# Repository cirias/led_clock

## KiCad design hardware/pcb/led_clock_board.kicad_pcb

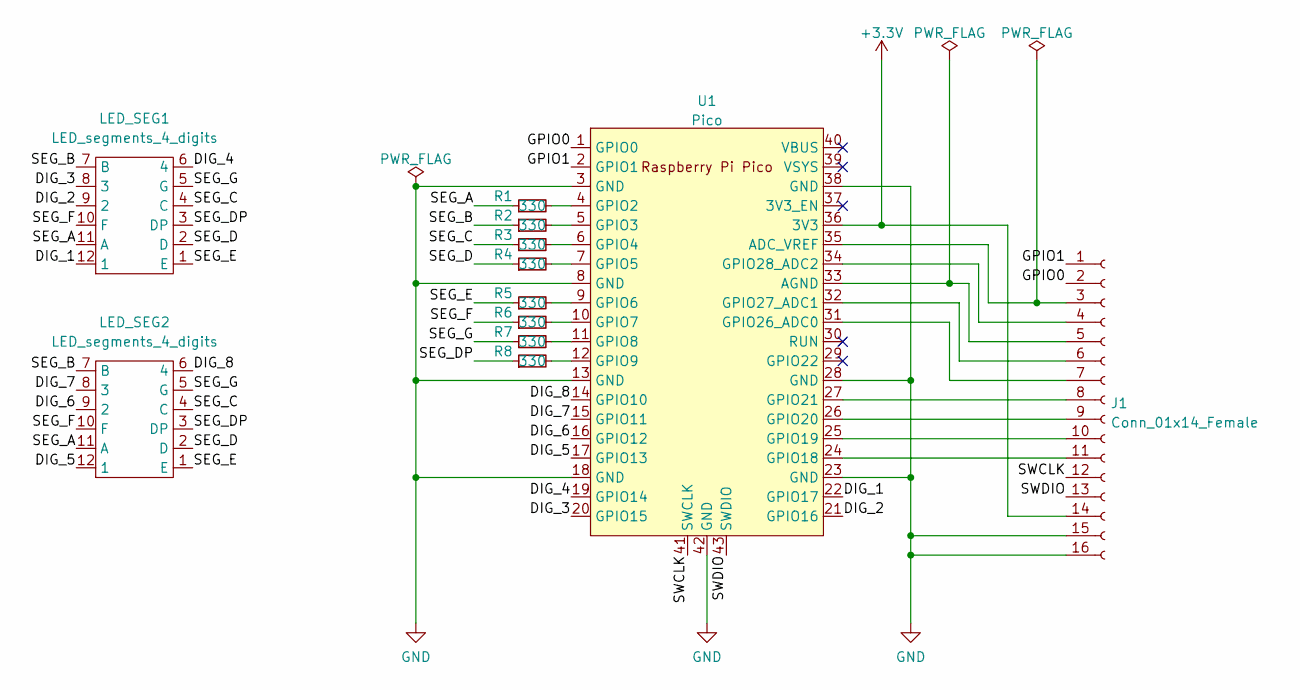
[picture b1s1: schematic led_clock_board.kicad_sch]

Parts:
J1: Conn_01x14_Female; PinHeader_1x16_P2.54mm_Vertical
LED_SEG1, LED_SEG2: LED_segments_4_digits
R1, R2, R3, R4, R5, R6, R7, R8: 330; R_Axial_DIN0207_L6.3mm_D2.5mm_P7.62mm_Horizontal
U1: Pico; RPi_Pico_SMD_TH

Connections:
+3V3: J1.14, U1.36 (3V3)
/DIG_1: LED_SEG1.12 (1), U1.22 (GPIO17)
/DIG_2: LED_SEG1.9 (2), U1.21 (GPIO16)
/DIG_3: LED_SEG1.8 (3), U1.20 (GPIO15)
/DIG_4: LED_SEG1.6 (4), U1.19 (GPIO14)
/DIG_5: LED_SEG2.12 (1), U1.17 (GPIO13)
/DIG_6: LED_SEG2.9 (2), U1.16 (GPIO12)
/DIG_7: LED_SEG2.8 (3), U1.15 (GPIO11)
/DIG_8: LED_SEG2.6 (4), U1.14 (GPIO10)
/GPIO0: J1.2, U1.1 (GPIO0)
/GPIO1: J1.1, U1.2 (GPIO1)
/SEG_A: LED_SEG1.11 (A), LED_SEG2.11 (A), R1.1
/SEG_B: LED_SEG1.7 (B), LED_SEG2.7 (B), R2.1
/SEG_C: LED_SEG1.4 (C), LED_SEG2.4 (C), R3.1
/SEG_D: LED_SEG1.2 (D), LED_SEG2.2 (D), R4.1
/SEG_DP: LED_SEG1.3 (DP), LED_SEG2.3 (DP), R8.1
/SEG_E: LED_SEG1.1 (E), LED_SEG2.1 (E), R5.1
/SEG_F: LED_SEG1.10 (F), LED_SEG2.10 (F), R6.1
/SEG_G: LED_SEG1.5 (G), LED_SEG2.5 (G), R7.1
/SWCLK: J1.12, U1.41 (SWCLK)
/SWDIO: J1.13, U1.43 (SWDIO)
GND: J1.15, J1.16, U1.3 (GND), U1.8 (GND), U1.13 (GND), U1.18 (GND), U1.23 (GND), U1.28 (GND), U1.38 (GND), U1.42 (GND)
unnamed: J1.3, U1.35 (ADC_VREF)
unnamed: J1.4, U1.34 (GPIO28_ADC2)
unnamed: J1.5, U1.33 (AGND)
unnamed: J1.6, U1.32 (GPIO27_ADC1)
unnamed: J1.7, U1.31 (GPIO26_ADC0)
unnamed: J1.8, U1.27 (GPIO21)
unnamed: J1.9, U1.26 (GPIO20)
unnamed: J1.10, U1.25 (GPIO19)
unnamed: J1.11, U1.24 (GPIO18)
unnamed: R1.2, U1.4 (GPIO2)
unnamed: R2.2, U1.5 (GPIO3)
unnamed: R3.2, U1.6 (GPIO4)
unnamed: R4.2, U1.7 (GPIO5)
unnamed: R5.2, U1.9 (GPIO6)
unnamed: R6.2, U1.10 (GPIO7)
unnamed: R7.2, U1.11 (GPIO8)
unnamed: R8.2, U1.12 (GPIO9)

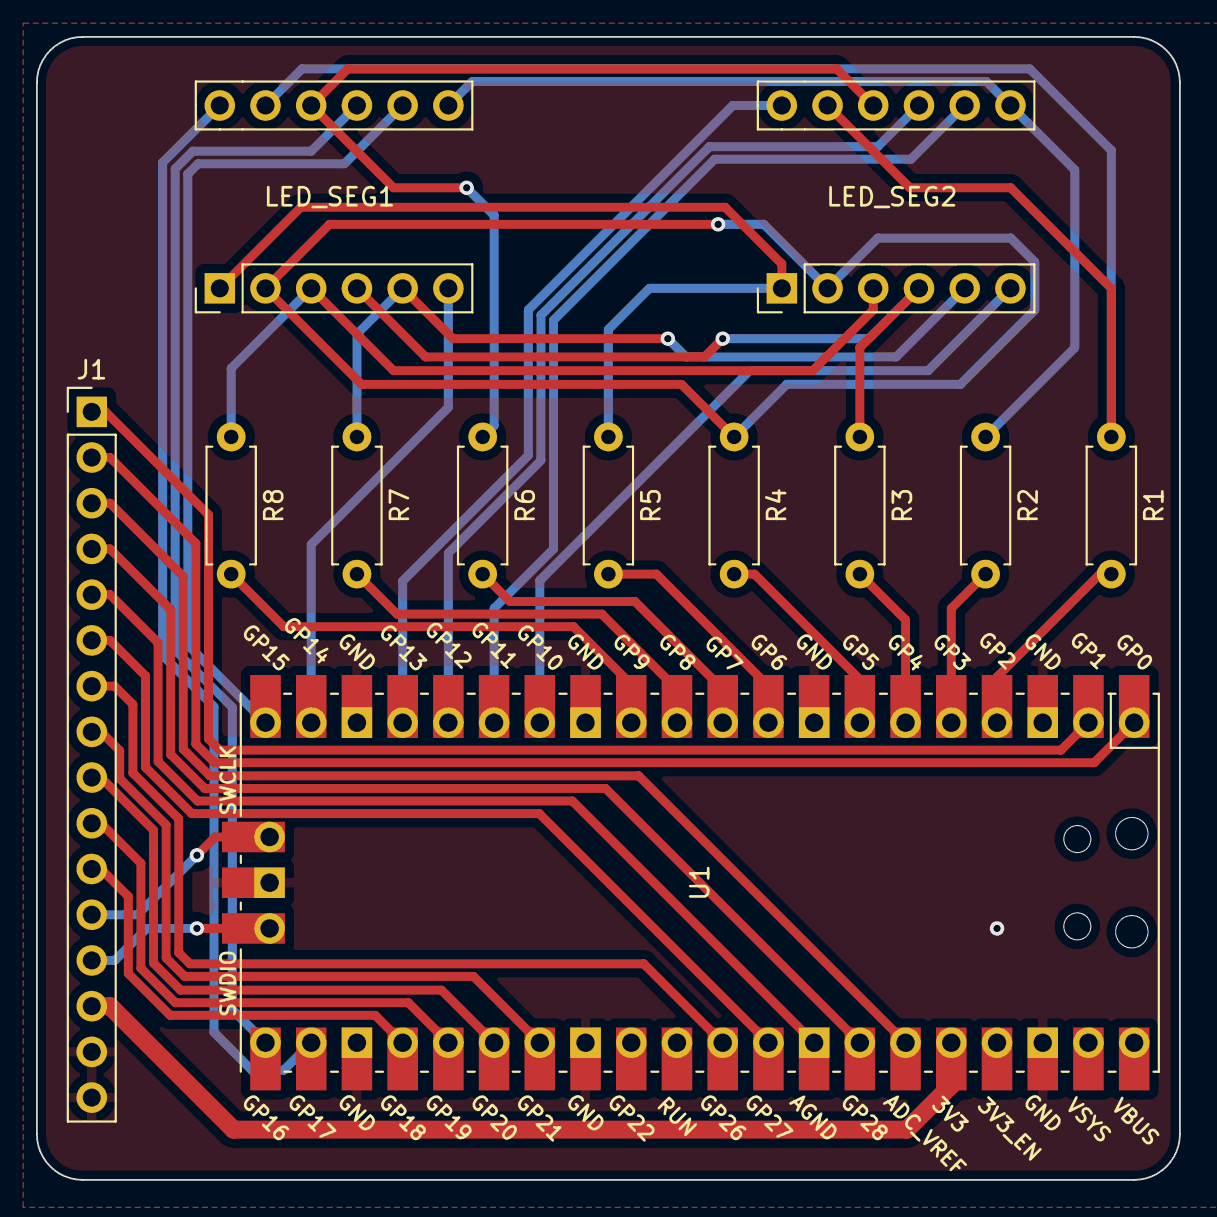
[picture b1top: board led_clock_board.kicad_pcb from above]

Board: 2 copper layers, 63.5 x 63.5 mm, 12 parts (0 on the bottom side), 39 nets.

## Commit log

2022-08-20 feat: Add firmware
2022-08-21 chore: Add datasheet for cd74hc4051
